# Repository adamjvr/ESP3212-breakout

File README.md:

# ESP3212-breakout
simple breakout for the ESP3212 modules, include 3V3 LDO, and pin headers female/male with breadboard spacing

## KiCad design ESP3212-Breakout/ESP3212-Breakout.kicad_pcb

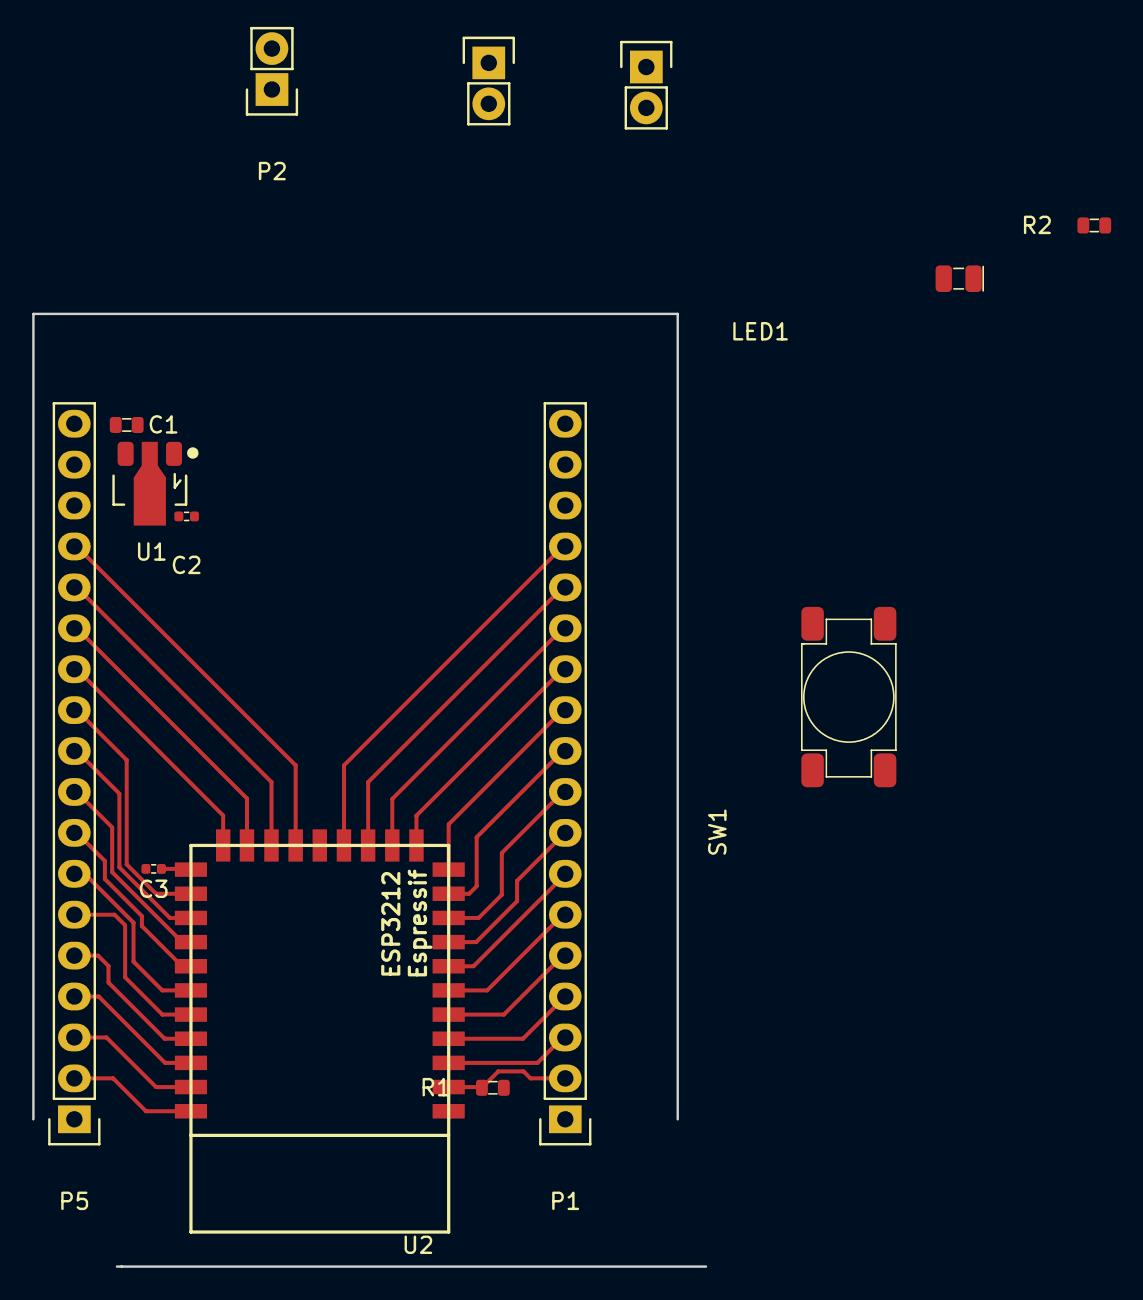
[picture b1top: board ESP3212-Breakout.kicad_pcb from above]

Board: 2 copper layers, 41.8 x 59.1 mm, 14 parts (0 on the bottom side), 31 nets.

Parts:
C1: CL10A106KQ8NNNC; C0603
C2: CL05B104JP5NNNC; C0402
C3: GRM155R71C104KA88D; C0402
LED1: 5988140107F; LED0805Y
P1, P5: CONN_01X18; Pin_Header_Straight_1x18
P2, P3, P4: CONN_01X02; Pin_Header_Straight_1x02
R1, R2: ERJ-3EKF1001V; R0603
SW1: TL3301AF160QG
U1: AZ1117CR-3.3TRG1_1; AZ1117CR-3.3TRG1
U2: ESP3212

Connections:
+3V3: C2.1, C3.1, P1.16, P5.16, R1.2, U1.2, U2.21
+5V: C1.1, P1.17, P5.17, U1.3
/IO25: P1.9, U2.9
/IO26: P1.10, U2.10
/IO27: P1.11, U2.11
/IO32: P1.7, U2.7
/IO33: P1.8, U2.8
/IO34: P1.5, U2.5
/IO35: P1.6, U2.6
/RXD: P5.5, U2.28
/TXD: P5.4, U2.29
GND: C1.2, C2.2, C3.2, P1.1, P1.18, P2.2, P3.2, P5.1, P5.2, P5.18, SW1.1, U1.1, U2.1, U2.16, U2.31
unnamed: P1.2, R1.1, SW1.2, U2.2
unnamed: P1.3, U2.3
unnamed: P1.4, U2.4
unnamed: P1.12, U2.12
unnamed: P1.13, U2.13
unnamed: P1.14, U2.14
unnamed: P1.15, U2.15
unnamed: P2.1, P5.14, U2.18
unnamed: P3.1, P5.15, U2.17
unnamed: P4.1, R2.2
unnamed: P5.3, U2.30
unnamed: P5.6, U2.27
unnamed: P5.7, U2.26
unnamed: P5.8, U2.25
unnamed: P5.9, U2.24
unnamed: P5.10, U2.23
unnamed: P5.11, U2.22
unnamed: P5.12, U2.20
unnamed: P5.13, U2.19

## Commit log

2016-10-31 Started
    Started a while ago, probably going to ancel it
